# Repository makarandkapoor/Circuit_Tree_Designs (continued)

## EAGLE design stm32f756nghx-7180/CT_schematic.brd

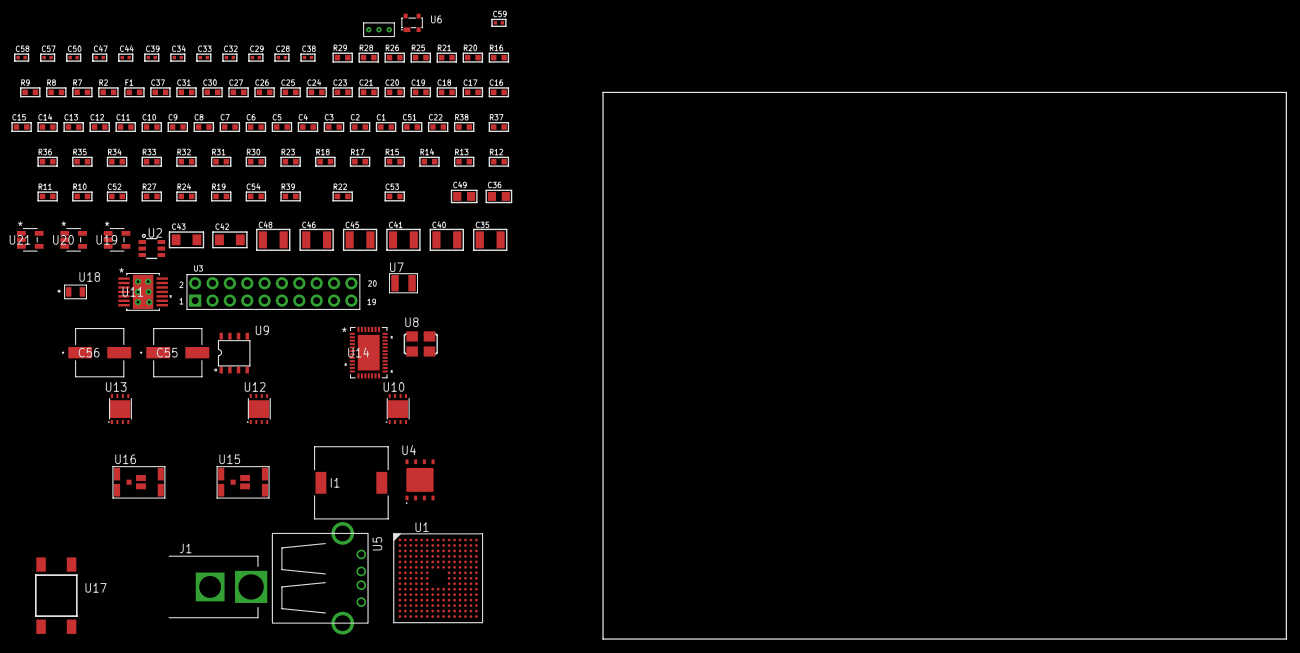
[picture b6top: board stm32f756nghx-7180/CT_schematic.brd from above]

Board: 2 copper layers, 100.0 x 80.0 mm, 118 parts (0 on the bottom side), 77 nets, no tracks yet.

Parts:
C1, C24, C30, C31, C37: 1e-06; C0603
C2, C3, C4, C5, C6, C7, C8, C9, C10, C11, C12, C13, C14, C15, C16, C17, C18, C19, C20, C21, C25, C26, C27: 1e-07; C0603
C22: 4.7e-06; C0603
C23: 1e-08; C0603
C28, C29: 1e-11; C0402
C32, C33, C34, C44, C47, C57, C58, C59: 1e-08; C0402
C35, C45, C46, C48: 1e-05; C1210
C36, C49: 1e-05; C0805
C38: 3.3e-09; C0402
C39, C50: 1e-07; C0402
C40, C41: 2.2e-05; C1210
C42, C43: 1e-05; C1206
C51: 2.2e-06; C0603
C52: 2.45e-08; R0603
C53: 2.8258362168397e-09; R0603
C54: 7.105e-09; R0603
C55, C56: 0.0001; EXV-9H
F1: 240.0; L0603
I1: 7e-06; DR1040
J1: PJ-037B; PJ-037B_PACKAGE
R2, R21, R26, R29: 1000.0; R0603
R7, R8, R9: 4700.0; R0603
R10: 47000.0; R0603
R11, R12, R13, R14, R15, R17, R18, R30, R32, R33, R36, R37, R38: 10000.0; R0603
R16: 1270.0; R0603
R19, R24, R27: 100000.0; R0603
R20, R28: 200.0; R0603
R22: 71007.101651032; R0603
R23: 22000.0; R0603
R25: 3900.0; R0603
R31: 75000.0; R0603
R34, R35: 95300.0; R0603
R39: 120272.72727273; R0603
U1: STM32F756NGH6; TFBGA216
U2: MAX4995AAUT+T; SOT-23-6
U3: arducam_ov2640; ARDUCAM
U4: MX25R6435FZAIH0; WSON-8-PAD
U5: 61400416021; USB-A-H
U6: prtr5v0u2ax; SOT143B
U7: ABS07-32.768KHZ-7-T
U8: ASFL1-25MHZ-NCS; ASFL1
U9: idt74fct38072; IDT74FCT38072
U10, U12, U13: LP3878SDX-ADJ/NOPB; WSON-8
U11: tps54225PWP; HTSSOP14
U14: LTC2928CUHF#PBF; QFN-38_UHF
U15, U16: IRF8306MTRPbF; IRF8306MTRPBF
U17: 4-1437565-2; SW_4-1437565-2
U18: Q65110A2395; LGM67K-G1J2-24-Z
U19, U20, U21: nc7sz125m5x; NC7SZ125M5X
U22: Dummy; DUMMY_PACKAGE_251

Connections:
CLK_CRYSTAL_U1_E1: C28.1, U1.E1, U7.1
CLK_CRYSTAL_U1_F1: C29.1, U1.F1, U7.2
CLK_U1_G1: U1.G1, U9.6
CLK_U3_8: U3.8, U9.7
CLK_U9_3: U8.3, U9.3
GND: C1.2, C2.2, C3.2, C4.2, C5.2, C6.2, C7.2, C8.2, C9.2, C10.2, C11.2, C12.2, C13.2, C14.2, C15.2, C16.2, C17.2, C18.2, C19.2, C20.2, C21.2, C22.2, C23.2, C24.2, C25.2, C26.2, C27.2, C28.2, C29.2, C30.2, C31.2, C32.2, C33.2, C34.2, C35.2, C36.2, C37.2, C38.2, C40.2, C41.2, C42.2, C43.2, C44.2, C45.2, C46.2, C47.2, C48.2, C49.2, C50.2, C51.2, C52.2, C53.2, C54.2, C55.2, C56.2, C57.2, C58.2, C59.2, J1.2, R2.2, R10.2, R11.2, R15.2, R16.2, R21.2, R23.2, R26.2, R29.2, R31.2, R34.2, R35.2, R36.2, R37.2, R38.2, U1.D15, U1.F2, U1.F6, U1.F7, U1.F8, U1.F9, U1.F10, U1.G6, U1.G10, U1.H6, U1.H10, U1.J6, U1.J10, U1.K6, U1.K7, U1.K8, U1.K9, U1.K10, U1.L6, U1.M1, U1.N1, U2.2, U3.2, U3.20, U4.4, U4.PAD, U5.4, U5.5, U5.6, U6.1, U8.2, U9.4, U9.5, U9.8, U10.3, U10.PAD, U11.5, U11.8, U11.9, U11.15, U12.3, U12.PAD, U13.3, U13.PAD, U14.8, U14.9, U14.10, U14.12, U14.13, U14.24, U14.25, U14.30, U14.32, U14.39, U18.C, U19.1, U19.3, U20.1, U20.3, U21.1, U21.3, U22.1
NET_U1_E5: R12.1, U1.E5
NET_U1_E6: R11.1, U1.E6
NET_U1_E11: C27.1, U1.E11
NET_U1_J1: R8.1, U1.J1, U20.4
NET_U1_L5: R13.1, U1.L5
NET_U1_R1: C23.1, C24.1, F1.1, U1.P1, U1.R1
NET_U1_R15: U17.3, U17.4
NET_U2_3: R10.1, U2.3
NET_U3_19: R9.1, U3.19, U21.4
NET_U4_7: R7.1, U1.K2, U4.7, U19.4
NET_U10_1: C34.1, U10.1
NET_U10_6: R20.2, R21.1, U10.6
NET_U10_8: R19.1, U10.8
NET_U11_2: R22.2, R23.1, U11.2
NET_U11_3: C37.1, U11.3
NET_U11_4: C38.1, U11.4
NET_U11_10: C39.1, I1.1, U11.10, U11.11
NET_U11_12: C39.2, U11.12
NET_U12_1: C44.1, U12.1
NET_U12_6: R25.2, R26.1, U12.6
NET_U12_8: R24.1, U12.8
NET_U13_1: C47.1, U13.1
NET_U13_6: R28.2, R29.1, U13.6
NET_U13_8: R27.1, U13.8
NET_U14_3: R37.1, U14.3
NET_U14_6: R34.1, U14.6
NET_U14_7: R35.1, U14.7
NET_U14_16: R36.1, R39.1, U14.16
NET_U14_18: R33.1, U14.18
NET_U14_19: R32.1, U14.19, U14.20
NET_U14_21: R30.1, R31.1, U14.21, U19.2, U20.2, U21.2
NET_U14_22: C50.1, R30.2, R32.2, R33.2, U14.11, U14.22
NET_U14_26: C53.1, U14.26
NET_U14_27: C52.1, U14.27
NET_U14_28: C54.1, U14.28
NET_U14_38: R38.1, U14.38
NET_U15_3: U14.2, U15.3
NET_U16_3: U14.37, U16.3
NET_U17_1: R2.1, U17.1, U17.2
PROC_DCMI_D0: U1.H15, U3.18
PROC_DCMI_D1: R16.1, U1.D15, U3.17
PROC_DCMI_D2: U1.A6, U3.16
PROC_DCMI_D3: U1.A5, U3.15
PROC_DCMI_D4: U1.A1, U3.14
PROC_DCMI_D5: U1.C3, U3.13
PROC_DCMI_D6: U1.A7, U3.12
PROC_DCMI_D7: U1.B2, U3.11
PROC_DCMI_D8: U1.B14, U3.10
PROC_DCMI_D9: U1.A12, U3.9
PROC_DCMI_HSYNC: U1.N4, U3.6
PROC_DCMI_PIXCLK: U1.P3, U3.7
PROC_DCMI_VSYNC: U1.B5, U3.5
PROC_GPIO_TO_U1_USB_FAULT: R14.1, R15.1, U1.A4, U2.6
PROC_GPIO_TO_U1_VBUS_EN: R15.1, U1.A2, U2.4
PROC_QUADSPI_BK1_IO0: U1.F14, U4.5
PROC_QUADSPI_BK1_IO1: U1.L2, U4.2
PROC_QUADSPI_BK1_IO2: R18.1, U1.A3, U4.3
PROC_QUADSPI_BK1_NCS: R17.1, U1.B6, U4.1
PROC_QUADSPI_CLK: U1.M5, U4.6
PROC_TIM1_CH1: U1.F15, U22.2
PROC_TIM1_CH2N: U1.R5, U22.3
PROC_USB_OTG_FS_DM: U5.2, U6.3
PROC_USB_OTG_FS_DP: U5.3, U6.2
PROC_USB_OTG_FS_VBUS: U2.1, U5.1, U6.4
VCC_14V6: C51.1, C55.1, C56.1, J1.1, R39.2, U14.23, U15.1, U15.2, U15.6, U15.7, U16.1, U16.2, U16.6, U16.7
VCC_S1_14V6: C35.1, C42.1, C43.1, C45.1, R19.2, R24.2, U10.4, U11.7, U11.13, U11.14, U12.4, U15.4, U15.5
VCC_S2_14V6: C48.1, R27.2, U13.4, U16.4, U16.5
VCC_TIER1_1V2: C26.1, C36.1, R20.1, U1.L11, U10.5
VCC_TIER1_3V3: C1.1, C2.1, C3.1, C4.1, C5.1, C6.1, C7.1, C8.1, C9.1, C10.1, C11.1, C12.1, C13.1, C14.1, C15.1, C16.1, C17.1, C18.1, C19.1, C20.1, C21.1, C22.1, C25.1, C30.1, C31.1, C32.1, C33.1, C40.1, C41.1, C57.1, C58.1, C59.1, F1.2, I1.2, R7.2, R8.2, R9.2, R12.2, R13.2, R14.2, R17.2, R18.2, R22.1, U1.C1, U1.E7, U1.E8, U1.E9, U1.E10, U1.F4, U1.F5, U1.F11, U1.G5, U1.G11, U1.H5, U1.H11, U1.J5, U1.J11, U1.K5, U1.K11, U1.L7, U1.L8, U1.L9, U1.L10, U3.1, U4.8, U8.4, U9.1, U9.2, U11.1, U19.5, U20.5, U21.5
VCC_TIER1_5V0: C46.1, R25.1, U2.5, U12.5
VCC_TIER2_1V2: C49.1, R28.1, U13.5

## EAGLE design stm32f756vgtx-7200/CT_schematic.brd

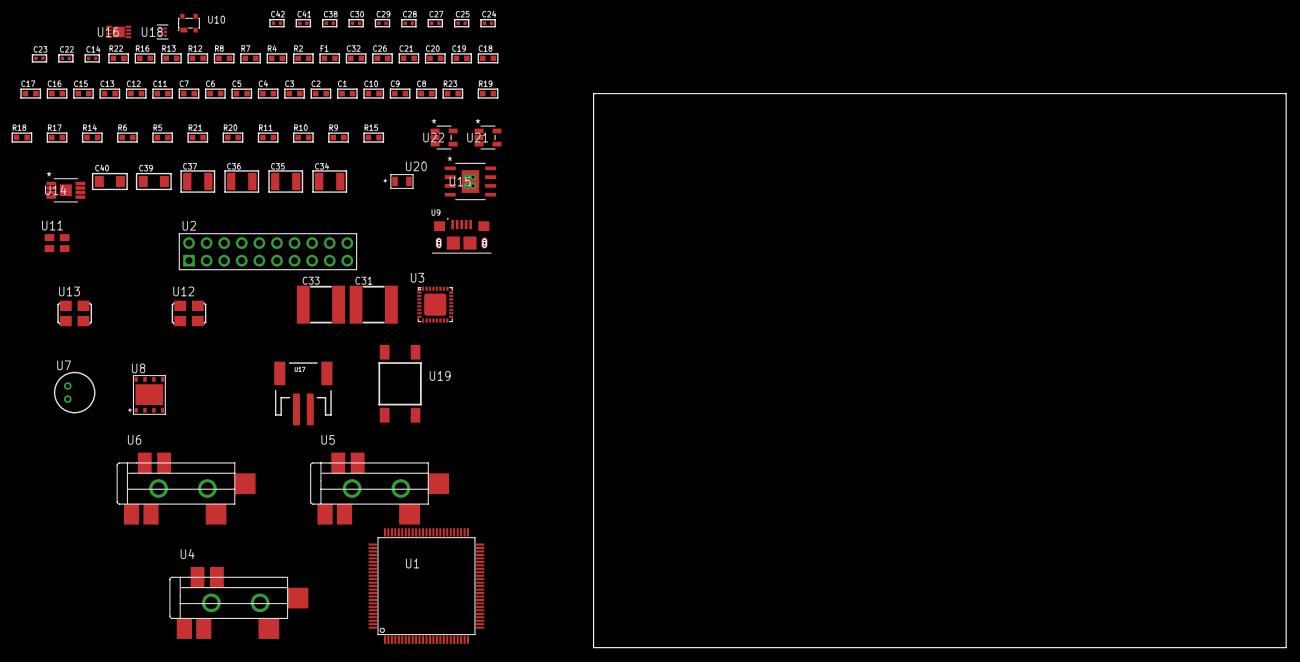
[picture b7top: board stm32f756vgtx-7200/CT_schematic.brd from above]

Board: 2 copper layers, 122.6 x 80.0 mm, 86 parts (0 on the bottom side), 50 nets, no tracks yet.

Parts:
C1, C12, C13, C15, C16, C17, C18, C19, C20, C21, C26, C32: 1e-06; C0603
C2, C3, C4, C5, C6, C7: 1e-07; C0603
C8: 4.7e-06; C0603
C9, C10: 2.2e-06; C0603
C11: 1e-08; C0603
C14, C22, C23, C24, C25, C27, C38: 1e-07; C0402
C28, C29, C30, C41, C42: 1e-08; C0402
C31, C33: 6.8e-05; 2220
C34, C35, C36, C37: 1e-05; C1210
C39, C40: 1e-05; C1206
F1: 240.0; L0603
R2: 1000.0; R0603
R4: 4700.0; R0603
R5, R6, R14, R17, R18, R23: 10000.0; R0603
R7, R8: 1270.0; R0603
R9, R10, R11: 100000.0; R0603
R12: 3900.0; R0603
R13, R16: 2200.0; R0603
R15: 4031.5447154472; R0603
R19: 82000.0; R0603
R20: 300000.0; R0603
R21: 120000.0; R0603
R22: 2000.0; R0603
U1: STM32F756VGT6; LQFP100
U2: TST-110-05-T-D-RA
U3: SGTL5000XNAA3; QFN-32
U4, U5, U6: SJ-43515TS-SMT-TR
U7: WM-64PCT; WM-64PC
U8: SST26WF016B-104I/MF; WFDN-8
U9: 10118193-0001LF; FCI_10118193-0001LF
U10: prtr5v0u2ax; SOT143B
U11: ASEK-32.768KHz-ECST; ASEK
U12: ASFL-24.57MHZ-NCS; ASFL1
U13: ASFL1-25MHZ-NCS; ASFL1
U14: MIC47100YMME; MSOP-8_EP
U15: MIC5234YME; SOIC-8_EP
U16: MCP73831T-2ACI/MC; DFN8_2X3MC
U17: S2B-PH-SM4-TB(LF)(SN); JST-2-SMD
U18: TPS3895ADRYR; SON-6
U19: 4-1437565-2; SW_4-1437565-2
U20: Q65110A2395; LGM67K-G1J2-24-Z
U21, U22: nc7sz125m5x; NC7SZ125M5X

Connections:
CLK_U1_8: U1.8, U11.3
CLK_U1_12: U1.12, U13.3
CLK_U3_21: U3.21, U12.3
GND: C1.2, C2.2, C3.2, C4.2, C5.2, C6.2, C7.2, C8.2, C9.2, C10.2, C11.2, C12.2, C13.2, C14.2, C22.2, C23.2, C24.2, C25.2, C26.2, C27.2, C28.2, C29.2, C30.2, C31.2, C32.2, C33.2, C34.2, C35.2, C36.2, C37.2, C38.2, C39.2, C40.2, C41.2, C42.2, R2.2, R5.2, R8.2, R13.2, R16.2, R19.2, R21.2, R22.2, U1.10, U1.19, U1.26, U1.49, U1.70, U1.74, U1.99, U2.4, U2.6, U2.8, U2.10, U2.12, U2.14, U2.16, U2.18, U2.20, U3.1, U3.3, U3.7, U3.EXP, U5.1, U6.1, U7.2, U8.4, U8.9, U9.5, U9.6, U9.7, U9.8, U9.9, U10.1, U11.2, U12.2, U13.2, U14.3, U14.EPAD, U15.7, U15.EPAD, U16.6, U16.9, U17.2, U18.2, U20.C, U21.2, U21.3, U22.1, U22.3
INPUT_USBPOWER_5V: C13.1, C39.1, R23.2, U1.68, U9.1, U10.4, U16.1, U16.2
NET_U1_14: R4.1, U1.14, U22.4
NET_U1_21: C11.1, C12.1, F1.1, U1.20, U1.21
NET_U1_48: C9.1, U1.48
NET_U1_73: C10.1, U1.73
NET_U1_94: R5.1, U1.94
NET_U1_98: U19.3, U19.4
NET_U3_10: C25.1, U3.10
NET_U3_29: R7.1, U3.29
NET_U3_31: R8.1, U3.31
NET_U4_1: U3.4, U4.1
NET_U4_2: U3.2, U4.2
NET_U4_5: U3.6, U4.5
NET_U5_2: C16.1, U5.2
NET_U5_5: C15.1, U5.5
NET_U6_2: C18.1, C19.1, U6.2
NET_U6_5: C17.1, U6.5
NET_U6_13: C18.2, C19.2
NET_U7_1: C20.1, C21.1, C26.1, U3.16, U7.1
NET_U7_15: C20.2, C21.2
NET_U14_6: R12.2, R13.1, U14.6
NET_U15_4: R15.2, R16.1, U15.4
NET_U16_5: R23.1, U16.5
NET_U16_8: R22.1, U16.8
NET_U18_1: R18.1, R19.1, U18.1
NET_U18_3: R20.2, R21.1, U18.3
NET_U18_4: R17.1, U18.4, U21.4, U22.2
NET_U19_1: R2.1, U19.1, U19.2
PROC_I2S1_CK: U1.29, U3.24
PROC_I2S1_SD: U1.31, U3.26
PROC_I2S1_WS: U1.28, U3.23
PROC_QUADSPI_BK1_IO0: U1.58, U8.5
PROC_QUADSPI_BK1_IO1: U1.59, U8.2
PROC_QUADSPI_BK1_IO2: R10.1, U1.1, U8.3
PROC_QUADSPI_BK1_IO3: R11.1, U1.23, U8.7
PROC_QUADSPI_BK1_NCS: R9.1, U1.92, U8.1
PROC_QUADSPI_CLK: U1.36, U8.6
PROC_SYS_JTCK_SWCLK: U1.76, U2.9
PROC_SYS_JTDO_SWO: U1.89, U2.13
PROC_SYS_JTMS_SWDIO: U1.72, U2.7
PROC_USB_OTG_FS_DM: U1.70, U9.2, U10.3
PROC_USB_OTG_FS_DP: U1.71, U9.3, U10.2
RST_OUT_U2_SRESET_B: R6.1, U2.15, U21.1
VCC_S1_3V7: C31.1, C32.1, C34.1, C35.1, C40.1, R14.1, R14.2, U14.1, U14.2, U14.4, U14.5, U15.5, U15.8, U16.3, U16.4, U17.1
VCC_TIER1_1V8: C1.1, C2.1, C3.1, C4.1, C5.1, C6.1, C7.1, C8.1, C14.1, C22.1, C23.1, C24.1, C27.1, C33.1, C38.1, C41.1, C42.1, F1.2, R4.2, R6.2, R7.2, R9.2, R10.2, R11.2, R12.1, R17.2, R18.2, R20.1, U1.6, U1.11, U1.27, U1.50, U1.75, U1.100, U2.1, U3.5, U3.20, U3.30, U8.8, U14.7, U14.8, U18.6, U21.5, U22.5
VCC_TIER1_3V3: C28.1, C29.1, C30.1, C36.1, C37.1, R15.1, U11.4, U12.4, U13.4, U15.1

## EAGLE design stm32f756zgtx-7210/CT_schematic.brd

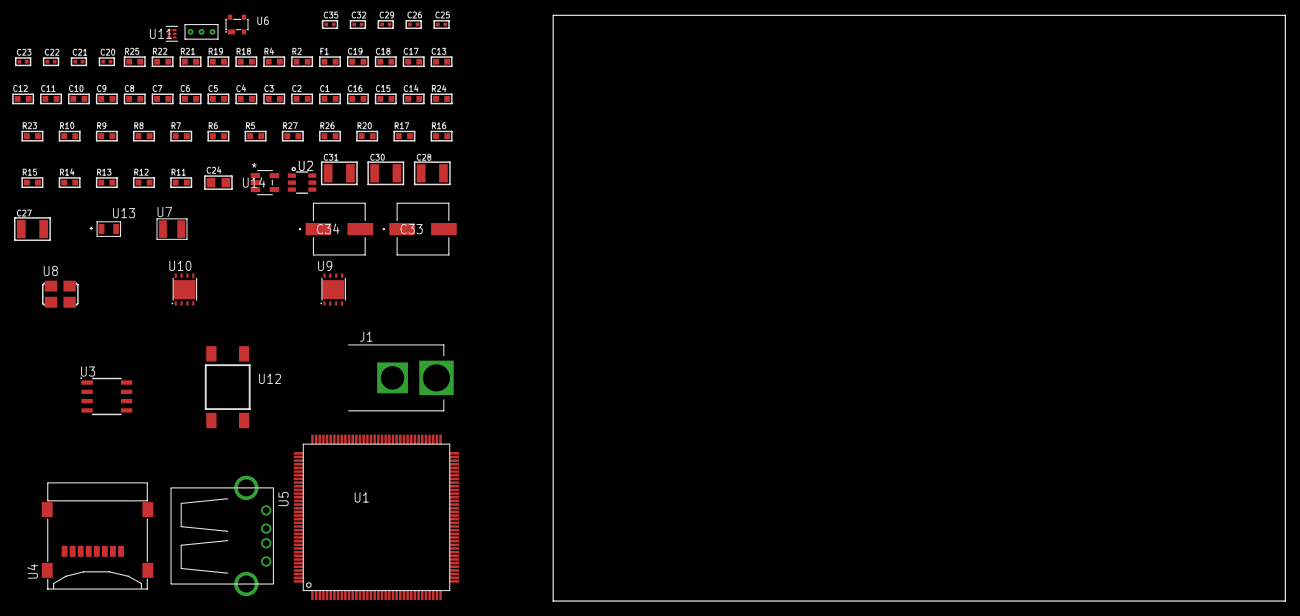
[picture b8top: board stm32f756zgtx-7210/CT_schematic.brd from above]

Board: 2 copper layers, 100.0 x 80.0 mm, 77 parts (0 on the bottom side), 44 nets, no tracks yet.

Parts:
C1, C18: 1e-06; C0603
C2, C3, C4, C5, C6, C7, C8, C9, C10, C11, C12, C13, C19: 1e-07; C0603
C14: 4.7e-06; C0603
C15, C16: 2.2e-06; C0603
C17: 1e-08; C0603
C20, C21: 1e-11; C0402
C22, C25, C26, C29, C35: 1e-08; C0402
C23, C32: 1e-07; C0402
C24: 1e-05; C0805
C27, C28, C30, C31: 1e-05; C1210
C33, C34: 0.0001; EXV-9H
F1: 240.0; L0603
J1: PJ-037B; PJ-037B_PACKAGE
R2, R19, R22: 1000.0; R0603
R4: 4700.0; R0603
R5: 47000.0; R0603
R6, R7, R8, R9, R10, R23, R24: 10000.0; R0603
R11, R12, R13, R14, R15, R16, R17, R20: 100000.0; R0603
R18: 2231.0; R0603
R21: 3900.0; R0603
R25: 9100.0; R0603
R26: 680000.0; R0603
R27: 120000.0; R0603
U1: STM32F756ZGT6; LQFP144
U2: MAX4995AAUT+T; SOT-23-6
U3: AT25010B-SSHL-T; SOIC-8
U4: 0472192001; MOLEX_47219-2001
U5: 61400416021; USB-A-H
U6: prtr5v0u2ax; SOT143B
U7: ABS07-32.768KHZ-7-T
U8: ASFL1-25MHZ-NCS; ASFL1
U9, U10: LP3878SDX-ADJ/NOPB; WSON-8
U11: TPS3895ADRYR; SON-6
U12: 4-1437565-2; SW_4-1437565-2
U13: Q65110A2395; LGM67K-G1J2-24-Z
U14: nc7sz125m5x; NC7SZ125M5X
U15: Dummy; DUMMY_PACKAGE_163

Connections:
CLK_CRYSTAL_U1_8: C20.1, U1.8, U7.1
CLK_CRYSTAL_U1_9: C21.1, U1.9, U7.2
CLK_U1_23: U1.23, U8.3
GND: C1.2, C2.2, C3.2, C4.2, C5.2, C6.2, C7.2, C8.2, C9.2, C10.2, C11.2, C12.2, C13.2, C14.2, C15.2, C16.2, C17.2, C18.2, C19.2, C20.2, C21.2, C22.2, C23.2, C24.2, C25.2, C26.2, C27.2, C28.2, C29.2, C30.2, C31.2, C32.2, C33.2, C34.2, C35.2, J1.2, R2.2, R5.2, R6.2, R19.2, R22.2, R25.2, R27.2, U1.16, U1.31, U1.38, U1.51, U1.61, U1.83, U1.94, U1.107, U1.120, U1.130, U2.2, U3.4, U4.6, U4.G1, U4.G2, U4.G3, U4.G4, U5.4, U5.5, U5.6, U6.1, U8.2, U9.3, U9.PAD, U10.3, U10.PAD, U11.2, U13.C, U14.1, U14.3, U15.1
NET_U1_25: R4.1, U1.25, U14.4
NET_U1_33: C17.1, C18.1, F1.1, U1.32, U1.33
NET_U1_71: C15.1, U1.71
NET_U1_106: C16.1, U1.106
NET_U1_138: R6.1, U1.138
NET_U1_142: U12.3, U12.4
NET_U1_143: R7.1, U1.143
NET_U2_3: R5.1, U2.3
NET_U3_3: R8.1, U3.3
NET_U3_7: R10.1, U3.7
NET_U9_1: C26.1, U9.1
NET_U9_6: R18.2, R19.1, U9.6
NET_U9_8: R17.1, U9.8
NET_U10_1: C29.1, U10.1
NET_U10_6: R21.2, R22.1, U10.6
NET_U10_8: R20.1, U10.8
NET_U11_1: R24.1, R25.1, U11.1
NET_U11_3: R26.2, R27.1, U11.3
NET_U11_4: R23.1, U11.4, U14.2
NET_U12_1: R2.1, U12.1, U12.2
PROC_GPIO_TO_U1_USB_FAULT: U1.2, U2.6
PROC_GPIO_TO_U1_VBUS_EN: U1.1, U2.4
PROC_PE4: U1.3, U15.2
PROC_PE5: U1.4, U15.3
PROC_SDMMC1_CK: R12.1, U1.113, U4.5
PROC_SDMMC1_CMD: R11.1, U1.116, U4.3
PROC_SDMMC1_D0: R13.1, U1.98, U4.7
PROC_SDMMC1_D1: R14.1, U1.99, U4.8
PROC_SDMMC1_D2: R15.1, U1.111, U4.1
PROC_SDMMC1_D3: R16.1, U1.112, U4.2
PROC_SPI1_MISO: U1.42, U3.2
PROC_SPI1_MOSI: U1.43, U3.5
PROC_SPI1_NSS: R9.1, U1.40, U3.1
PROC_SPI1_SCK: U1.41, U3.6
PROC_USB_OTG_FS_DM: U1.103, U5.2, U6.3
PROC_USB_OTG_FS_DP: U1.104, U5.3, U6.2
PROC_USB_OTG_FS_VBUS: U1.101, U2.1, U5.1, U6.4
VCC_S1_14V6: C27.1, C30.1, C33.1, C34.1, J1.1, R17.2, R20.2, U9.4, U10.4
VCC_TIER1_3V3: C1.1, C2.1, C3.1, C4.1, C5.1, C6.1, C7.1, C8.1, C9.1, C10.1, C11.1, C12.1, C13.1, C14.1, C19.1, C22.1, C23.1, C24.1, C25.1, C28.1, C32.1, C35.1, F1.2, R4.2, R7.2, R8.2, R9.2, R10.2, R11.2, R12.2, R13.2, R14.2, R15.2, R16.2, R18.1, R23.2, R24.2, R26.1, U1.6, U1.17, U1.30, U1.39, U1.52, U1.62, U1.72, U1.84, U1.95, U1.108, U1.121, U1.131, U1.144, U3.8, U4.4, U8.4, U9.5, U11.6, U14.5
VCC_TIER1_5V0: C31.1, R21.1, U2.5, U10.5
